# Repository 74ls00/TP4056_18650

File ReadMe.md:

Оригиналы чертежей в EAGLE. Только для разметки подключений.

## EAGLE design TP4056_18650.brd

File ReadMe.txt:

Оригиналы чертежей в EAGLE. Только для разметки подключений.

Импортированные и модифицированные платы в Sprint-Layout 6

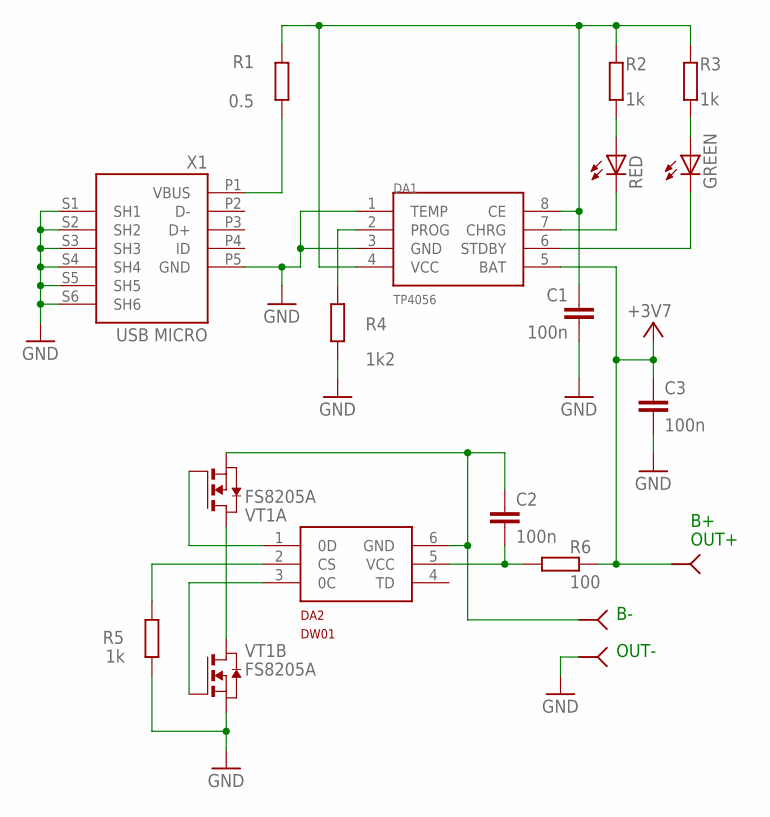
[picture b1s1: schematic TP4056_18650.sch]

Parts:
B+: B-; PAD-
B-: B-; PAD-
C1, C2, C3: 100n; C0805
DA1: TP4056; SOP-8
DA2: DW01A; SOT23-6
GND: B-; PAD-
GREEN: LEDCHIP-LED0805; CHIP-LED0805
R1: 0.5; R0805
R2, R3, R5: 1k; R0805
R4: 1k2; R0805
R6: 100; R0805
RED: LEDCHIP-LED0805; CHIP-LED0805
VT1: FS8205A; TSSOP-8
X1: USB MICRO; CON2_USB_MICRO_B_AT

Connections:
+3V7: B+.B-, C3.1, DA1.5 (BAT), R6.2
B-: B-.B-, C2.1, DA2.6 (GND), VT1.2 (S), VT1.3 (S)
GND: C1.2, C3.2, DA1.1 (TEMP), DA1.3 (GND), GND.B-, R4.1, R5.1, VT1.6 (S), VT1.7 (S), X1.P5 (GND), X1.S1 (SH1), X1.S2 (SH2), X1.S3 (SH3), X1.S4 (SH4), X1.S5 (SH5), X1.S6 (SH6)
unnamed: VT1.1 (D), VT1.8 (D)
unnamed: DA2.3 (0C), VT1.5 (G)
unnamed: C1.1, DA1.4 (VCC), DA1.8 (CE), R1.2, R2.2, R3.2
unnamed: DA2.1 (0D), VT1.4 (G)
unnamed: DA2.2 (CS), R5.2
unnamed: C2.2, DA2.5 (VCC), R6.1
unnamed: DA1.7 (CHRG), RED.C
unnamed: DA1.6 (STDBY), GREEN.C
unnamed: R2.1, RED.A
unnamed: GREEN.A, R3.1
unnamed: DA1.2 (PROG), R4.2
unnamed: R1.1, X1.P1 (VBUS)

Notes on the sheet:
OUT+
OUT-

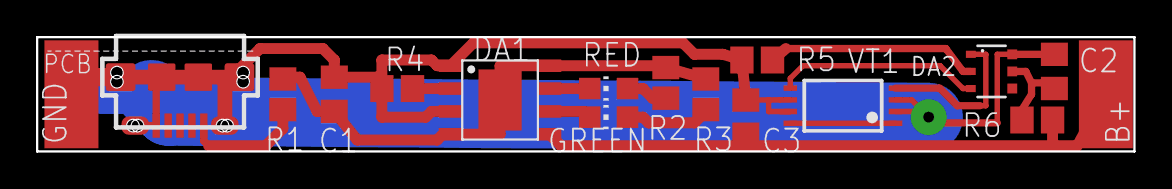
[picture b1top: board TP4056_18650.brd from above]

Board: 2 copper layers, 61.0 x 6.4 mm, 18 parts (1 on the bottom side), 15 nets.
